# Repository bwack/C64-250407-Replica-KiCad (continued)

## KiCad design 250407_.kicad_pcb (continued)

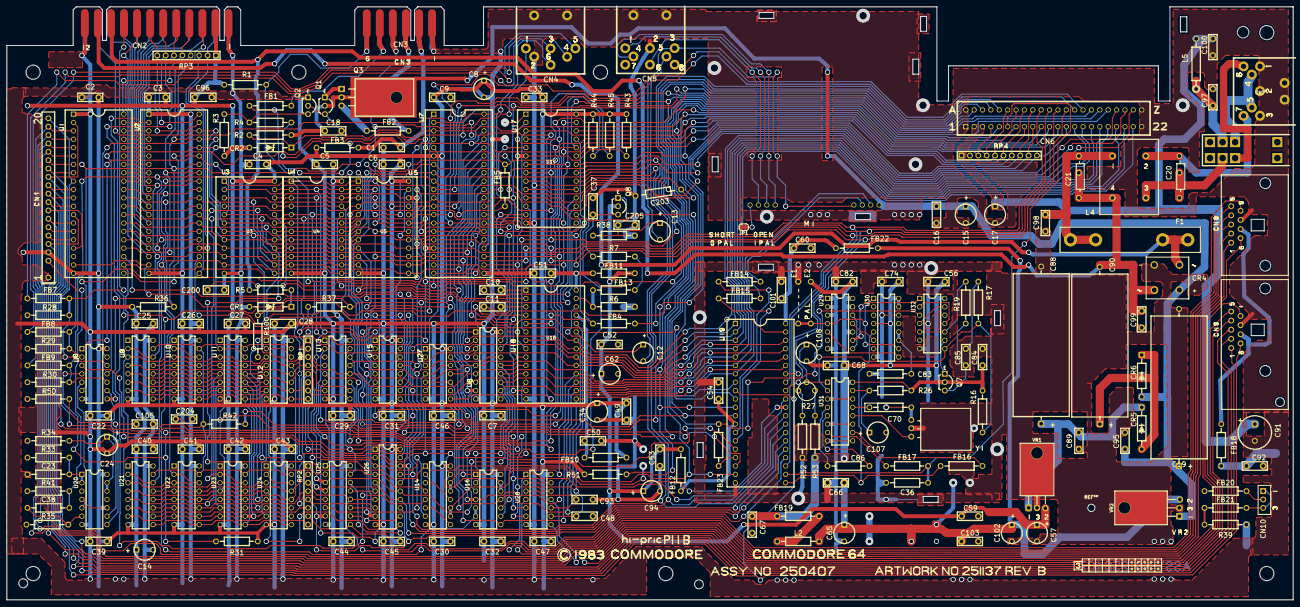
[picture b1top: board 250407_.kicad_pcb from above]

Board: 2 copper layers, 390.0 x 179.8 mm, 215 parts (0 on the bottom side), 227 nets.

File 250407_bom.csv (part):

Reference," Quantity"," Value"," Footprint",Mouser P/N,Reichelt P/N,Other
C96 C22 C47 C3 C2 C9 C105 C39 C46 C18 C1 C99 C98 C92 C95 C89 C59 C103 C68 C74 C67 C84 C56 C66 C82 C200 C44 C28 C43 C27 C42 C26 C41 C25 C40 C29 C4 C5 C6 C33 C31 C30 C7 C32 C45 C101 C60 C54 C53 C16 C49 C50 C52 C51,"54",".1","Cap MLCC 0.1uF 50V X7R P5.08mm Radial",80-C322C104K5R5TA or 581-SR215C104KART,X7R-5 100N,
C8 C24 C57 C102 C65 C17 C94 C15 C13 C34 C62 C12 C14 C107 C108,"15","10uF","Cap Alu 10uF 25V 5x5mm P2.5mm Radial",667-ECE-A1EKS100I,M 10U 25,
"C11 C10 ","2","470pF","Cap MLCC 470pF X7R Axial",594-A471K15X7RF5UAA,?,
"C19 ","1","2200uF","Cap Elyt 2200uF 16V 15x30mm Axial",594-2222-021-16222 or 594-2222-021-15222 or 598-228TTA016M,COS 105 2200/16,
"C203 ","1","?","KU-14194HB-RevB-KiCad:CAPACITOR_RADIAL_P13.97_L9.9_D3.6",~,,
"C204 ","1","?","KU-14194HB-RevB-KiCad:CAP_P5.08mm",~,,
"C205 ","1","220pF","KU-14194HB-RevB-KiCad:CAP_P5.08mm",~,,
"C21 C20 ","2",".22","Cap Polyester Film 0.22uF 63VAC P10mm",594-2222-368-25224,MKS4-100 220N2,
"C23 ","1","360pF","Cap MLCC 350pF 50V C0G Axial",594-A331J15C0GF5TAA,?,
"C36 ","1","20pF","Cap MLCC 20pF C0G Axial",581-SA102A200JAR,?,
"C37 ","1","1000pF","KU-14194HB-RevB-KiCad:CAP_P5.08mm",~,,
"C38 ","1","51pF","Cap MLCC 51pF (47pF OK) X7R Axial",581-SA102A470JAR,?,
"C48 C93 ","2","1800pF","Cap MLCC 1800pF X7R Axial",581-SA101C182KAR,?,
"C70 ","1","15pF 5%","Cap MLCC 15pF 50V 5% C0G Axial/Radial Leaded",594-A150J15C0GH5TAA,KERKO 15P,
"C85 ","1",".47","Cap MLCC 0.47uF +80/-20% X7R P5.08mm Radial","80-C330C474K5R or 81-RCER71H474K1K1H3B ",Z5U-5 470N,
"C86 C83 ","2","82pF","Cap MLCC 82pF 100V C0G Axial / Radial Disc",80-C410C820J1G,,
"C88 ","1","1000uF","Cap Elyt 1000uF 16V 20% 10x30mm Axial",594-2222-021-15102 or 598-108TTA016M,,
"C90 ","1","470uF","Cap Elyt 470uF 50V 20% 13x26mm Axial",598-477TTA050M,COS 105 470/50,
"C91 ","1","100uF","Cap Elyt 100uF 16V 20% 6.3x11mm Radial",REA101M1CBK-0611P,FR-A 100U 16,
"C97 C100 ","2",".22","Cap MLCC 0.22uF 50V X7R P5.08mm Radial",80-C330C224K1R,Z5U-5 220N,
"CN1 ","1","KEYBOARD_20PIN_MALE","Pin Header 20 POS P2.54mm male vertical",538-22-28-4204,MPE 087-1-020,
"CN10 ","1","LED_CONNECTOR","Pin Header 3 POS P2.54mm male vertical",538-22-28-4033,RND 205-00624,
"CN2 ","1","USER_PORT_CON","KU-14194HB-RevB-KiCad:EDGE_CON_24P",-,,
"CN3 ","1","CASSETTE_PORT_CON","KU-14194HB-RevB-KiCad:EDGE_CON_12P_TAPE",-,,
"CN4 ","1","SERIAL_BUS_CON","KU-14194HB-RevB-KiCad:SERIAL_CON_DIN6",,,
"CN5 ","1","AV_CONN","KU-14194HB-RevB-KiCad:AV_CON_DIN8",-,,
"CN6 ","1","EXPANSION_PORT","Conn Edge Dual Female 44 POS P2.54mm",,Digikey: H122591-ND,
"CN7 ","1","POWER_CON","KU-14194HB-RevB-KiCad:POWER_CON_D7_250407",,,
"CN8 CN9 ","2","CONTROL_PORT","Standard Connector DSUB E09P RA590",571-5747467-1,,
"CR1 ","1","IN4371","Zener Diode 2.7V 500mW DO-35-2",78-TZX2V7A,"ZF 2,7",
"CR100 CR102 CR101 CR103 ","4","D_Small_ALT",,~,,
"CR2 ","1","IN755","Zener Diode 7.5V 500mW DO-35-2",78-TZX7V5C,"ZF 7,5",
"CR4 ","1","BRIDGE_RECTIFIER","Bridge Rectifier 2A 600V Vf=1.05V",627-S2VB60-5000,KBPC604 DIO,
CR5 CR6,"2","1N4001","Rectifier 1A Vr=50V",625-1N4001-E3/54 or 625-1N4001-E3/53,,
"E1 ","1","JUMPER_WIRE","KU-14194HB-RevB-KiCad:JUMPER_WIRE",-,,
"E2 ","1","JUMPER_WIRE_DASHED","KU-14194HB-RevB-KiCad:JUMPER_WIRE",-,,
"F1 ","2","1A","Fuse Clips (buy two)",504-BK/1A1907-03-R,,
"FB18 FB4 FB22 FB12 FB14 FB15 FB13 FB10 FB11 ","9","FERRITE_BEAD","Ferrite Bead D3.5 L4.45mm Axial",623-2743001112LF or 81-BL01RN1A2A2B,BEAD 8-21,
"FB7 FB9 FB8 FB5 FB2 FB1 FB3 FB20 FB21 FB17 FB16 FB19 FB23 ","13","FERRITE_NARROW","Ferrite Bead D3.5 L4.45mm Axial",623-2743001112LF or 81-BL01RN1A2A2B,BEAD 8-21,
"JP1 ","1","Jumper_NC_Small","Jumper:SolderJumper-2_P1.3mm_Bridged_RoundedPad1.0x1.5mm",~,,
"L2 ","1","2.2uH","Inductor 2.2uH 5% Radial",652-78F2R2J-RC,"L-MICC 2,2µ",
"L4 ","1","CHOKE","Common Mode Choke 250V 3.8mH 2.1A 150mOhms",80-SSR10V-21038,,
"L5 ","1","1.2uH","Inductor 1.5uH 10% Radial",542-5800-4R7-RC,"L-HBCC 1,5µ",
"M1 ","1","MODULATOR_LONGBOARD","KU-14194HB-RevB-KiCad:MODULATOR_PORT_LONGBOARD",-,,
"Q2 Q1 Q7 Q8 ","4","2SC1815","Bipolar Transistor TO-92 Vce=60V 400mA",2SC1815,SC 1815,
"Q3 ","1","TP29B/2SD880","Bipolar Transistor TO-220",512-KSD880YTU,SD 880,
"R1 R43 R44 R45 ","4","3K3","Resistor 3K3 0207 Axial",594-MBB02070C3301FC1,"METALL 3,30K",
R17 R37,"2","2K7","Resistor 2K7 0207 Axial",594-MBB02070C2701FCT,"METALL 2,70K",
"R19 ","1","15K","Resistor 15K 0207 Axial",594-MBB02070C1502FC1,"METALL 15,0K",
"R2 R51 ","2","1.5K","Resistor 1K5 0207 Axial",594-MBB02070C1501FCT,"1W 1,5K",
"R26 R53 ","2","100","Resistor 100 0207 Axial",594-MBB02070C1000FCT,METALL 100,
"R27 ","1","500","Trimmer Resistor 500 Ohms Linear",652-3306F-1-501,BOU 3386P-1-501,
"R28 R30 R29 R36 R4 R16 R100 R31 R38 R6 ","10","1K","Resistor 1K 0207 Axial",594-MBB02070C1001FCT,"METALL 1,00K",
"R3 R7 ","2","10K","Resistor 10K 0207 Axial",594-MBB02070C1002FCT,"METALL 10,0K",
"R33 R34 ","2","47K","Resistor 47K 0207 Axial",594-MBB02070C4702FC1,"METALL 47,0K",
"R35 ","1","470K","Resistor 470K 0207 Axial",594-MBB02070C4703FCT,METALL 470K,
"R39 ","1","390","Resistor 390 0207 Axial",594-MBB02070C3900FCT,METALL 390,
"R41 R50 ","2","1M","Resistor 1M 0207 Axial",594-MBB02070C1004FCT or 603-HHV-25JT-52-1M,,
"R42 ","1","~","KU-14194HB-RevB-KiCad:RESISTOR",-,-,
"R5 ","1","560","Resistor 560 0207 Axial",594-MBB02070C5600FCT,METALL 560,
"R52 ","1","330","Resistor 330 0207 Axial",594-MBB02070C3300FCT,,
"RP1 RP2 ","2","33","Resistor Network 33R Isolated 8 pin SIP",652-4308R-2LF-33 or 268-33-RC,,
"RP3 ","1","R_ARRAY_7WAY_US","Resistor Network 3K3 Bussed 8 pin SIP",774-77081332P,,
"RP4 ","1","R_ARRAY_9WAY_US","Resistor Network 3K3 Bussed 10 pin SIP",774-770101332P,,
"SW1 ","1","POWER_SWITCH","KU-14194HB-RevB-KiCad:POWER_SWITCH",,,
"U1 ","1","CIA_U1","KU-14194HB-RevB-KiCad:DIP40",-,,
"U12 U24 U11 U23 U10 U22 U21 U9 ","8","4164-2","KU-14194HB-RevB-KiCad:DIP16",-,,
"U14 ","1","74LS258","QUADRUPLE 2-LINE TO 1-LINE DATA SELECTORS/MULTIPLEXERS","595-SN74LS258BN ",,
"U15 ","1","74LS139","DUAL 2-LINE TO 4-LINE DECODERS/MULTIPLEXERS","595-SN74LS139AN ",,
"U17 ","1","PLA_U17","KU-14194HB-RevB-KiCad:DIP28",-,,
"U18 ","1","6581","KU-14194HB-RevB-KiCad:DIP28",-,,
"U19 ","1","VIC","KU-14194HB-RevB-KiCad:DIP40",-,,
"U2 ","1","CIA_U2","KU-14194HB-RevB-KiCad:DIP40",-,,
"U20 ","1","556","DUAL PRECISION TIMERS","595-NE556N ",,
"U25 U13 ","2","74LS257","QUADRUPLE 2-LINE TO 1-LINE DATA SELECTORS/MULTIPLEXERS","595-SN74LS257BN ",,
"U26 ","1","74LS373","OCTAL D-TYPE TRANSPARENT LATCHES AND EDGE-TRIGGERED FLIP-FLOPS","595-SN74LS373N ",,
"U27 ","1","7408","QUADRUPLE 2-INPUT POSITIVE-AND GATES","595-SN74LS08N ",,
"U28 U16 ","2","4066","CMOS Quad Bilateral Switch","595-CD4066BE ",,
"U29 ","1","74LS74","DUAL D-TYPE POSITIVE-EDGE-TRIGGERED FLIP-FLOPS WITH PRESET AND CLEAR","595-SN74LS74AN ",,
"U3 U4 ","2","2364A","KU-14194HB-RevB-KiCad:DIP24 BASIC AND KERNAL ROM",-,,
"U30 ","1","74LS193","SYNCHRONOUS 4-BIT UP/DOWN COUNTERS (DUAL CLOCK WITH CLEAR)","595-SN74LS193N ",,
"U31 ","1","74LS629N","VOLTAGE-CONTROLLED OSCILLATORS","595-SN74LS629N ",,
"U32 ","1","MC4044","KU-14194HB-RevB-KiCad:DIP14",-,,
"U5 ","1","2332A","KU-14194HB-RevB-KiCad:DIP24 CHAR ROM",-,,
"U6 ","1","2114","KU-14194HB-RevB-KiCad:DIP18 COLOR RAM",-,,
"U7 ","1","6510_MPU","KU-14194HB-RevB-KiCad:DIP40",-,,
"U8 ","1","7406N","HEX INVERTER BUFFERS/DRIVERSWITH OPEN-COLLECTOR HIGH-VOLTAGE OUTPUTS","595-SN7406N ",,
"VR1 ","1","7812","Linear Voltage Regulators 12V 1A Positive","863-MC7812CTG ",,
"VR2 ","1","7805","Linear Voltage Regulators 5V 1A Positive","863-MC7805CTG ",,
"Y1 ","1","Crystal","Crystals HC49/U","815-AB-17.734475-B4 ",,
,,,,,,
Other:,,,,,,
,"Quantity",,"Description",mouser,,
,"4",,"Socket PDIP 40P P2.54mm W15.24mm DUAL WIPE",517-4840-6000-CP,,
,"2",,"Socket PDIP 28P P2.54mm W15.24mm DUAL WIPE",517-4828-6000-CP,,
,"3",,"Socket PDIP 24P P2.54mm W15.24mm DUAL WIPE",517-4824-6000-CP,,
,"1",,"Socket PDIP 20P P2.54mm W7.62mm DUAL WIPE",517-4820-3000-CP,,
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
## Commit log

2021-04-20 the interactive bom added
2021-04-20 gitignore
2021-04-20 Added interactive bom link in readme.
2021-04-20 small change
2021-04-20 ibom preview
2021-05-22 svg file
2021-05-22 update svg
2021-05-22 screenshots
2021-06-19 Rev 1.1 release
2021-06-19 3D models
2021-06-19 remove gitignore
2021-08-01 Added rescue lib, and removed from gitignore #1
2021-08-24 TP29B #2
2022-07-31 Fixed pin names in 4164 symbols
2022-07-31 Correct Input/Output pin type for 74LS258
2022-07-31 Correct pin types for many ICs to reduce the numebr or ERC errors and warnings
2022-07-31 Additional changes to the pin properties. Now only 11 warning in the ERC check.
2022-08-10 Fix north PCB edge
2022-08-18 Update schematics version and readme
2022-08-20 updated second schematics Revision and comment
2022-08-24 replaced CR5, CR6, F1 and CN10 with symbols closer to original schematics
2022-08-24 add labels to ROML, ROMH, I/O1 and I/O2
2022-12-04 Updated README.md. left out values
